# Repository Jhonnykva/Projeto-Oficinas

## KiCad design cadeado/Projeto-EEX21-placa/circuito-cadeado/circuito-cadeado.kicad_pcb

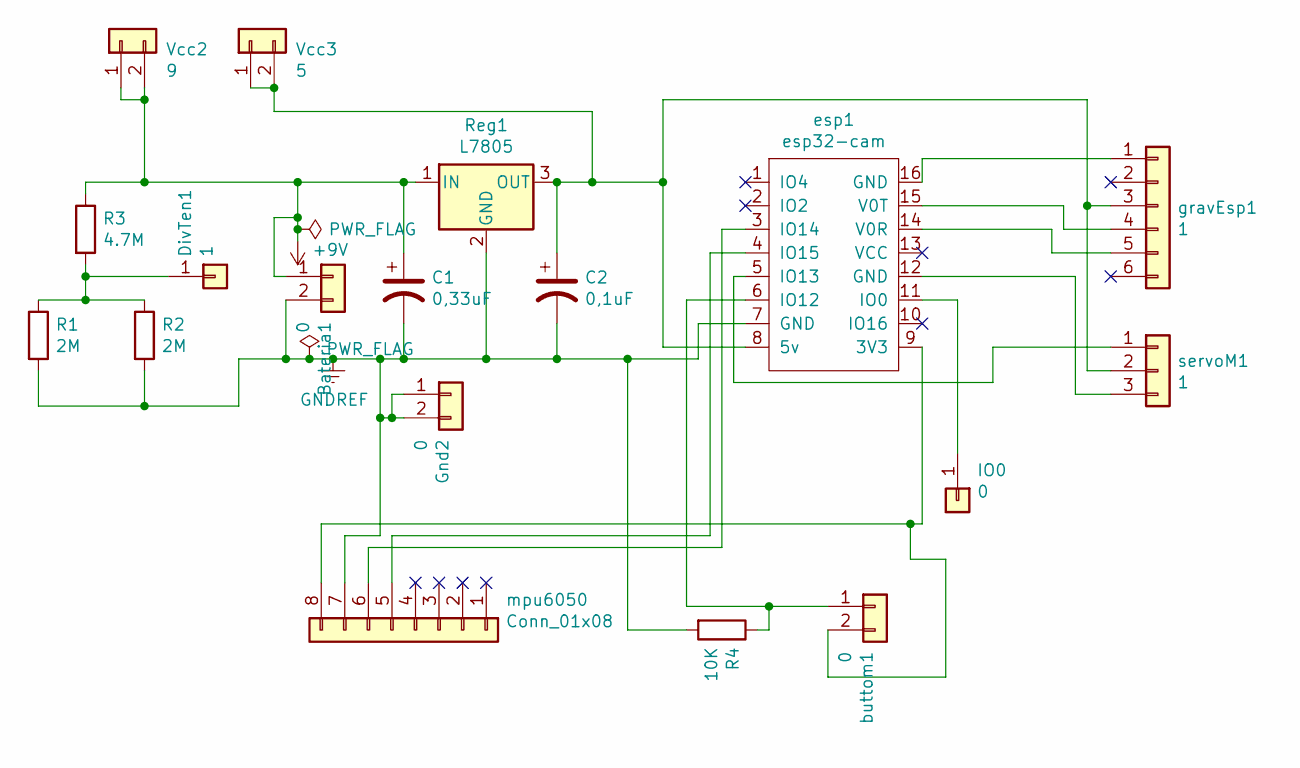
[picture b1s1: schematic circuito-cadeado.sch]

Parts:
Bateria1: 0; PinSocket_1x02_P2.54mm_Vertical
C1: 0,33uF; C_Disc_D3.0mm_W2.0mm_P2.50mm
C2: 0,1uF; C_Disc_D3.0mm_W2.0mm_P2.50mm
DivTen1: 1; PinSocket_1x01_P2.54mm_Vertical
Gnd2: 0; PinSocket_1x02_P2.54mm_Vertical
IO0: 0; PinSocket_1x01_P2.54mm_Vertical
R1, R2: 2M; R_Axial_DIN0204_L3.6mm_D1.6mm_P7.62mm_Horizontal
R3: 4.7M; R_Axial_DIN0204_L3.6mm_D1.6mm_P7.62mm_Horizontal
R4: 10K; R_Axial_DIN0204_L3.6mm_D1.6mm_P7.62mm_Horizontal
Reg1: L7805; lm7805
Vcc2: 9; PinSocket_1x02_P2.54mm_Vertical
Vcc3: 5; PinSocket_1x02_P2.54mm_Vertical
buttom1: 0; PinSocket_1x02_P2.54mm_Vertical
esp1: esp32-cam; ESP32CAM
gravEsp1: 1; PinSocket_1x06_P2.54mm_Vertical
mpu6050: Conn_01x08; PinSocket_1x09_P2.54mm_Vertical
servoM1: 1; PinSocket_1x03_P2.54mm_Vertical

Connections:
+9V: Bateria1.1, C1.1, R3.1, Reg1.1 (IN), Vcc2.1, Vcc2.2
GNDREF: Bateria1.2, C1.2, C2.2, Gnd2.1, Gnd2.2, R1.2, R2.2, R4.2, Reg1.2 (GND), esp1.7 (GND), mpu6050.7
unnamed: C2.1, Reg1.3 (OUT), Vcc3.1, Vcc3.2, esp1.8 (5v), gravEsp1.3, servoM1.2
unnamed: DivTen1.1, R1.1, R2.1, R3.2
unnamed: IO0.1, esp1.11 (IO0)
unnamed: R4.1, buttom1.1, esp1.6 (IO12)
unnamed: buttom1.2, esp1.9 (3V3), mpu6050.8
unnamed: esp1.3 (IO14), mpu6050.6
unnamed: esp1.4 (IO15), mpu6050.5
unnamed: esp1.5 (IO13), servoM1.1
unnamed: esp1.12 (GND), servoM1.3
unnamed: esp1.14 (V0R), gravEsp1.5
unnamed: esp1.15 (V0T), gravEsp1.4
unnamed: esp1.16 (GND), gravEsp1.1

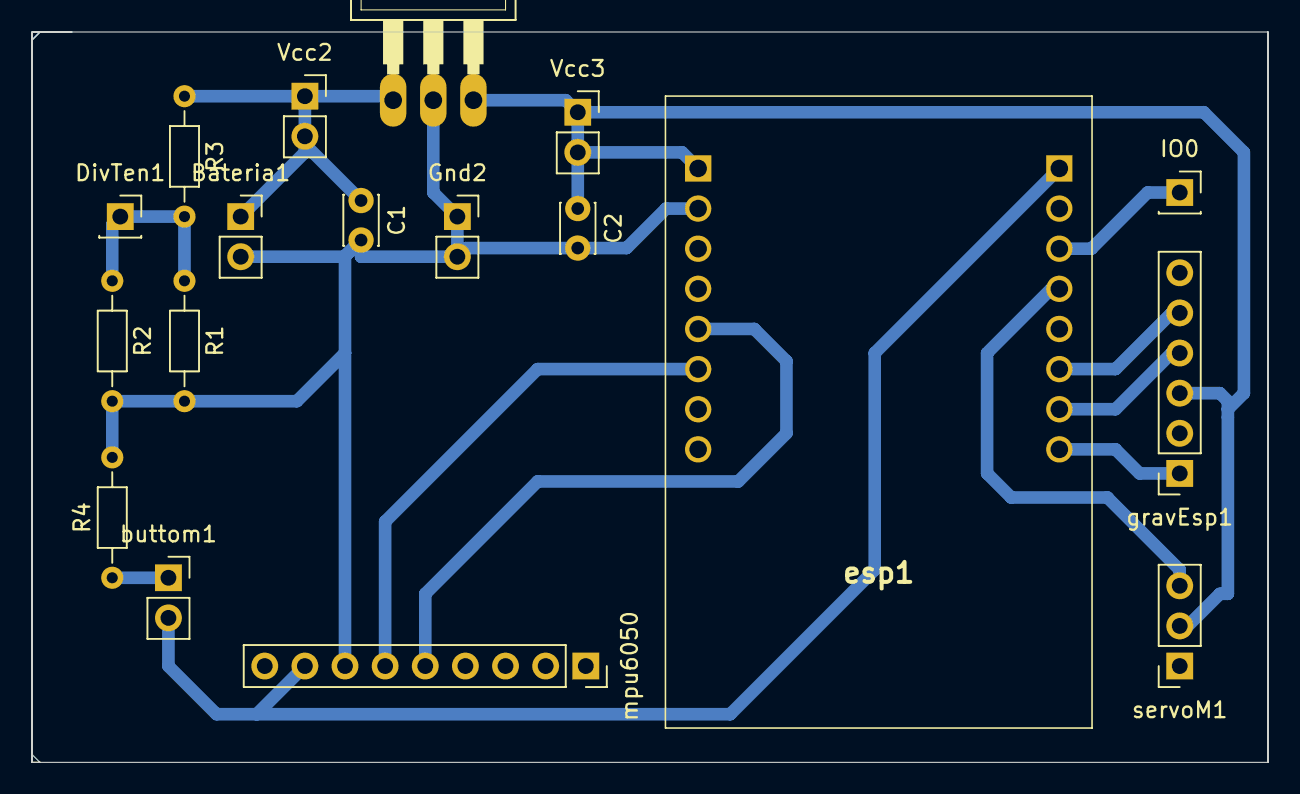
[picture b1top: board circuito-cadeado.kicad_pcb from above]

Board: 2 copper layers, 78.2 x 46.2 mm, 18 parts (0 on the bottom side), 14 nets.

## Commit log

2021-09-08 Estrutura base para API
2021-09-09 Serviços para registro & login de usuario
    O serviço de registro falta ser limitado para usuarios existentes
2021-09-09 Serviços para criar, atualizar e obter cadeados
2021-09-09 Serviços para registro & uso dos códigos liberadores
2021-09-10 Hardware
2021-09-11 Serviço para verificar se o liberador é válido
2021-09-12 Consulta p/ verificar se o código liberador é válido
2021-09-12 Consulta p/ verificar se o código liberador é válido 2
2021-09-13 Serviço para verificar se o cadeado está desbloqueado
2021-09-13 Estrutura inicial app web
2021-09-14 Listado de cadeados do usuario
2021-09-14 Cors habilitado no servidor de API
2021-09-14 Relação entre cadeado e liberador
2021-09-14 Serviços para controle de eventos (inicial)
2021-09-14 Listado de liberadores & eventos
2021-09-15 Criação de eventos
2021-09-15 Formulários para registrar cadeados e liberadores
2021-09-15 Geração de código qr para associar cadeado
2021-09-15 Serviço para obter informação de usuario
2021-09-15 Controles adicionais no serviço para obter eventos
2021-09-15 Lista de eventos de todos os cadeados do usuario
2021-09-18 Modelagem base 3D
2021-09-19 modelagem3d v1.1
2021-09-19 Serviço para procesar cod qr do liberador no servidor
2021-09-19 modelagem3D v1.2
2021-09-21 Função para verificar se existe um liberador valido
2021-09-21 Página para visualização do liberador individualmente
2021-09-22 Ajustes na deteção de movimentos
2021-09-22 Correção de autorização de cadeado
2021-09-22 Mudança na geração de qr de cofiguração
2021-09-22 Funções de controle do servo
2021-09-27 Update cadeado-esp.ino
    salvando e carregando dados permanentes, se ocorrer algum problema me avisa.
2021-10-01 Update cadeado-esp.ino
    resolvendo problemas EEPROM
2021-10-01 Serviço para qr de configuração
2021-10-01 Uso das funções para gravar/ler flash & leitura de qr de configuração
2021-11-06 modelos
2021-11-10 projeto da placa
2021-11-11 atualização circuito impresso v1.1
2021-11-19 Correções na plataforma
2021-11-19 Controle de tensão de bateria
2021-11-19 Evento de baixa nível de carga da bateria
2021-11-19 Bloqueio do cadeado
2021-11-21 Modelo 3d
2021-11-25 Modelo 3D atualizado
2021-11-29 Ajuste na associação do cadeado
2021-12-03 Envio de email
2021-12-03 Ajuste na descrição dos eventos
2021-12-04 Controla tempo minimo entre eventos predeterminados
2021-12-06 Modelo atualizado
2021-12-14 Organização do código
2021-12-14 Notificação nos eventos de bloquear/desbloquear
